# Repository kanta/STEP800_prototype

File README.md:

# STEP800_prototype

This repository has been retained for data storage, but is no longer being updated.

Please visit https://github.com/ponoor/STEP800.

---

8 axis stepper motor driver board which can control over Ethernet. The current firmware is based on [Open Sound Control](http://opensoundcontrol.org/) protocol.
[Arduino Zero](https://www.arduino.cc/en/Guide/ArduinoZero) and official [Ethernet library](https://www.arduino.cc/en/reference/ethernet) compatible.

Stepper driver chips are STMicroelectronics's [L6470](https://www.st.com/en/motor-drivers/l6470.html) which provide most of functionalities as a stepper driver.

# Repository Contents

# Documentation

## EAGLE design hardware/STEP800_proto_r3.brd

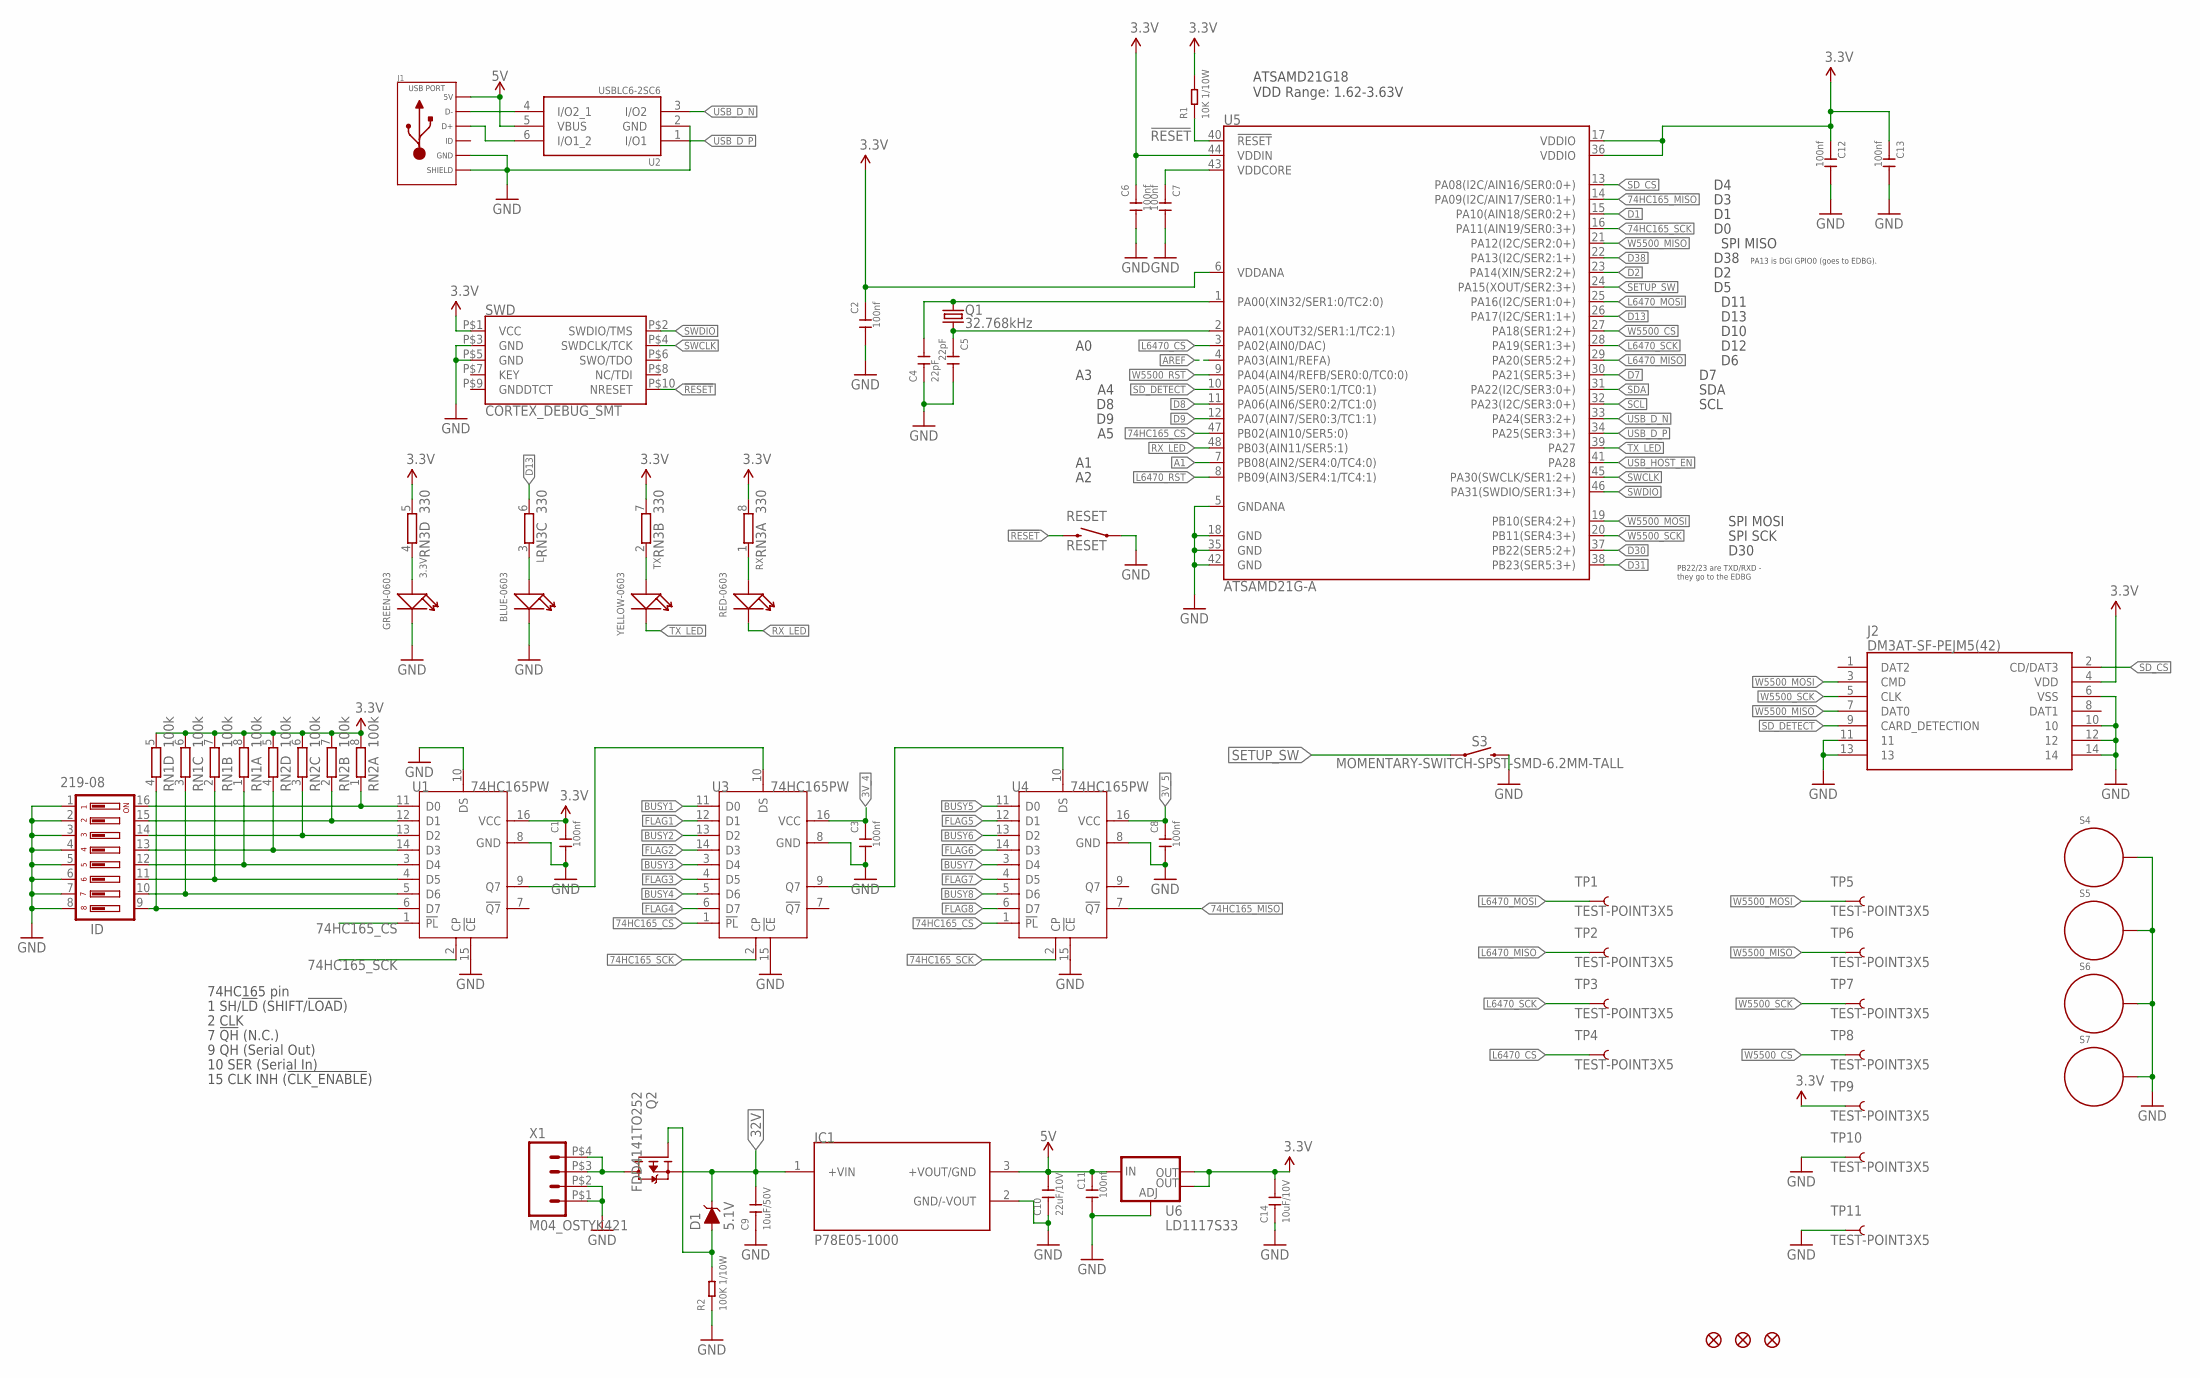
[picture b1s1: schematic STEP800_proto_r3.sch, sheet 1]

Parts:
3.3V: GREEN-0603; LED-0603
C1, C2, C3, C6, C7, C8, C11, C12, C13: 100nf; C0402
C4, C5: 22pF; C0402
C9: 10uF/50V; C1206
C10: 22uF/10V; C1206
C14: 10uF/10V; C0805
D1: 5.1V; SOD-323
FD1, FD2, FD3: FIDUCIAL1X2; FIDUCIAL-1X2
IC1: P78E05-1000; CONV_P78E05-1000
ID: 219-08; CTS-219-08
J1: USB_MICRO_10118193-0001LF; MICROUSB-FCI-PBAN
J2: DM3AT-SF-PEJM5(42); DM3ATSFPEJM542
L: BLUE-0603; LED-0603
Q1: 32.768kHz; FC-135
Q2: FDD4141TO252; TO252
R1: 10K 1/10W; R0603
R2: 100K 1/10W; R0603
RESET: RESET; TACTILE-SWITCH-SMD
RN1, RN2: 100k; CAY16_LONG_W
RN3: 330; CAY16_LONG_W
RX: RED-0603; LED-0603
S3: MOMENTARY-SWITCH-SPST-SMD-6.2MM-TALL; TACTILE_SWITCH_SMD_6.2MM_TALL
S4, S5, S6, S7: STANDOFF_ELECTRICAL; STANDOFF-ELECTRICAL
SWD: CORTEX_DEBUG_SMT; 20021121-00010C4LF
TP1, TP2, TP3, TP4, TP5, TP6, TP7, TP8, TP9, TP10, TP11: TEST-POINT3X5; PAD.03X.05
TX: YELLOW-0603; LED-0603
U1, U3, U4: 74HC165PW; TSSOP16
U2: USBLC6-2SC6; SOT23-6L
U5: ATSAMD21G-A; TQFP-48
U6: LD1117S33; SOT223
X1: M04_OSTYK421; OSTYK42104030

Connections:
3.3V: C1.1, C2.1, C6.1, C12.1, C13.1, C14.2, J2.4 (VDD), R1.2, RN1.5 (2), RN1.6 (2), RN1.7 (2), RN1.8 (2), RN2.5 (2), RN2.6 (2), RN2.7 (2), RN2.8 (2), RN3.5 (2), RN3.7 (2), RN3.8 (2), SWD.P$1 (VCC), TP9.P$1, U1.16 (VCC), U5.6 (VDDANA), U5.17 (VDDIO), U5.36 (VDDIO), U5.44 (VDDIN), U6.2 (OUT), U6.4 (OUT); also elsewhere on the board
3V_4: C3.1, U3.16 (VCC); also elsewhere on the board
3V_5: C8.1, U4.16 (VCC); also elsewhere on the board
5V: C10.2, C11.1, IC1.3 (+VOUT/GND), J1.1 (5V), U2.5 (VBUS), U6.3 (IN); also elsewhere on the board
32V: C9.2, D1.C, IC1.1 (+VIN), Q2.2 (S); also elsewhere on the board
74HC165_CS: U1.1 (!PL), U3.1 (!PL), U4.1 (!PL), U5.47 (PB02(AIN10/SER5:0))
74HC165_MISO: U4.7 (!Q7), U5.14 (PA09(I2C/AIN17/SER0:1+))
74HC165_SCK: U1.2 (CP), U3.2 (CP), U4.2 (CP), U5.16 (PA11(AIN19/SER0:3+))
!RESET: R1.1, RESET.3 (2), SWD.P$10 (NRESET), U5.40 (!RESET!)
A1: U5.7 (PB08(AIN2/SER4:0/TC4:0))
AREF: U5.4 (PA03(AIN1/REFA))
BUSY1: U3.11 (D0); also elsewhere on the board
BUSY2: U3.13 (D2); also elsewhere on the board
BUSY3: U3.3 (D4); also elsewhere on the board
BUSY4: U3.5 (D6); also elsewhere on the board
BUSY5: U4.11 (D0); also elsewhere on the board
BUSY6: U4.13 (D2); also elsewhere on the board
BUSY7: U4.3 (D4); also elsewhere on the board
BUSY8: U4.5 (D6); also elsewhere on the board
D1: U5.15 (PA10(AIN18/SER0:2+))
D2: U5.23 (PA14(XIN/SER2:2+))
D7: U5.30 (PA21(SER5:3+))
D8: U5.11 (PA06(AIN6/SER0:2/TC1:0))
D9: U5.12 (PA07(AIN7/SER0:3/TC1:1))
D13: RN3.6 (2), U5.26 (PA17(I2C/SER1:1+))
D30: U5.37 (PB22(SER5:2+))
D31: U5.38 (PB23(SER5:3+))
D38: U5.22 (PA13(I2C/SER2:1+))
D+1: J1.3 (D+), U2.6 (I/O1_2)
FLAG1: U3.12 (D1); also elsewhere on the board
FLAG2: U3.14 (D3); also elsewhere on the board
FLAG3: U3.4 (D5); also elsewhere on the board
FLAG4: U3.6 (D7); also elsewhere on the board
FLAG5: U4.12 (D1); also elsewhere on the board
FLAG6: U4.14 (D3); also elsewhere on the board
FLAG7: U4.4 (D5); also elsewhere on the board
FLAG8: U4.6 (D7); also elsewhere on the board
GND: 3.3V.-, C1.2, C2.2, C3.2, C4.1, C5.2, C6.2, C7.2, C8.2, C9.1, C10.1, C11.2, C12.2, C13.2, C14.1, IC1.2 (GND/-VOUT), ID.1, ID.2, ID.3, ID.4, ID.5, ID.6, ID.7, ID.8, J1.5 (GND), J1.S1 (SLD), J1.S2 (SLD), J1.S3 (SLD), J1.S4 (SLD), J1.S5 (SLD), J1.S6 (SLD), J1.S7 (SLD), J1.S8 (SLD), J2.6 (VSS), J2.10, J2.11, J2.12, J2.13, J2.14, L.-, R2.1, RESET.1, S3.B2 (2), S4.P1, S5.P1, S6.P1, S7.P1, SWD.P$3 (GND), SWD.P$5 (GND), TP10.P$1, TP11.P$1, U1.8 (GND), U1.10 (DS), U1.15 (!CE), U2.2 (GND), U3.8 (GND), U3.15 (!CE), U4.8 (GND), U4.15 (!CE), U5.5 (GNDANA), U5.18 (GND), U5.35 (GND), U5.42 (GND), U6.1 (ADJ), X1.P$1 (1), X1.P$2 (2); also elsewhere on the board
L6470_CS: TP4.P$1, U5.3 (PA02(AIN0/DAC)); also elsewhere on the board
L6470_MISO: TP2.P$1, U5.29 (PA20(SER5:2+)); also elsewhere on the board
L6470_MOSI: TP1.P$1, U5.25 (PA16(I2C/SER1:0+)); also elsewhere on the board
L6470_RST: U5.8 (PB09(AIN3/SER4:1/TC4:1)); also elsewhere on the board
L6470_SCK: TP3.P$1, U5.28 (PA19(SER1:3+)); also elsewhere on the board
unnamed: C4.2, Q1.P$2 (2), U5.1 (PA00(XIN32/SER1:0/TC2:0))
unnamed: ID.16, RN2.1, U1.11 (D0)
unnamed: D1.A, Q2.1 (G), R2.2
unnamed: ID.15, RN2.2 (1), U1.12 (D1)
unnamed: ID.14, RN2.3 (1), U1.13 (D2)
unnamed: C5.1, Q1.P$1 (1), U5.2 (PA01(XOUT32/SER1:1/TC2:1))
unnamed: U1.9 (Q7), U3.10 (DS)
unnamed: RN3.1, RX.+
unnamed: ID.13, RN2.4 (1), U1.14 (D3)
unnamed: ID.12, RN1.1, U1.3 (D4)
unnamed: ID.11, RN1.2 (1), U1.4 (D5)
unnamed: RN3.2 (1), TX.+
unnamed: L.+, RN3.3 (1)
unnamed: 3.3V.+, RN3.4 (1)
unnamed: J1.2 (D-), U2.4 (I/O2_1)
unnamed: ID.10, RN1.3 (1), U1.5 (D6)
unnamed: U3.9 (Q7), U4.10 (DS)
unnamed: ID.9, RN1.4 (1), U1.6 (D7)
RX_LED: RX.-, U5.48 (PB03(AIN11/SER5:1))
SCL: U5.32 (PA23(I2C/SER3:0+))
SDA: U5.31 (PA22(I2C/SER3:0+))
SD_CS: J2.2 (CD/DAT3), U5.13 (PA08(I2C/AIN16/SER0:0+))
SD_DETECT: J2.9 (CARD_DETECTION), U5.10 (PA05(AIN5/SER0:1/TC0:1))
SETUP_SW: S3.A2 (1), U5.24 (PA15(XOUT/SER2:3+))
SWCLK: SWD.P$4 (SWDCLK/TCK), U5.45 (PA30(SWCLK/SER1:2+))
SWDIO: SWD.P$2 (SWDIO/TMS), U5.46 (PA31(SWDIO/SER1:3+))
TX_LED: TX.-, U5.39 (PA27)
USB_D_N: U2.3 (I/O2), U5.33 (PA24(SER3:2+))
USB_D_P: U2.1 (I/O1), U5.34 (PA25(SER3:3+))
USB_HOST_EN: U5.41 (PA28)
VDDCORE1: C7.1, U5.43 (VDDCORE)
VRAW: Q2.3 (D), X1.P$3 (3), X1.P$4 (4)
W5500_CS: TP8.P$1, U5.27 (PA18(SER1:2+)); also elsewhere on the board
W5500_MISO: J2.7 (DAT0), TP6.P$1, U5.21 (PA12(I2C/SER2:0+)); also elsewhere on the board
W5500_MOSI: J2.3 (CMD), TP5.P$1, U5.19 (PB10(SER4:2+)); also elsewhere on the board
W5500_RST: U5.9 (PA04(AIN4/REFB/SER0:0/TC0:0)); also elsewhere on the board
W5500_SCK: J2.5 (CLK), TP7.P$1, U5.20 (PB11(SER4:3+)); also elsewhere on the board

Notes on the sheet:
PB22/23 are TXD/RXD - they go to the EDBG
PA13 is DGI GPIO0 (goes to EDBG).
ATSAMD21G18 VDD Range: 1.62-3.63V
D30
D12
D10
D11
D13
D38
SPI MISO
SPI MOSI
SPI SCK
SDA
SCL
1 SH/!LD! (SHIFT/!LOAD!)
2 CLK
7 !QH! (N.C.)
9 QH (Serial Out)
10 SER (Serial In)
15 CLK INH (!CLK_ENABLE!)
74HC165 pin

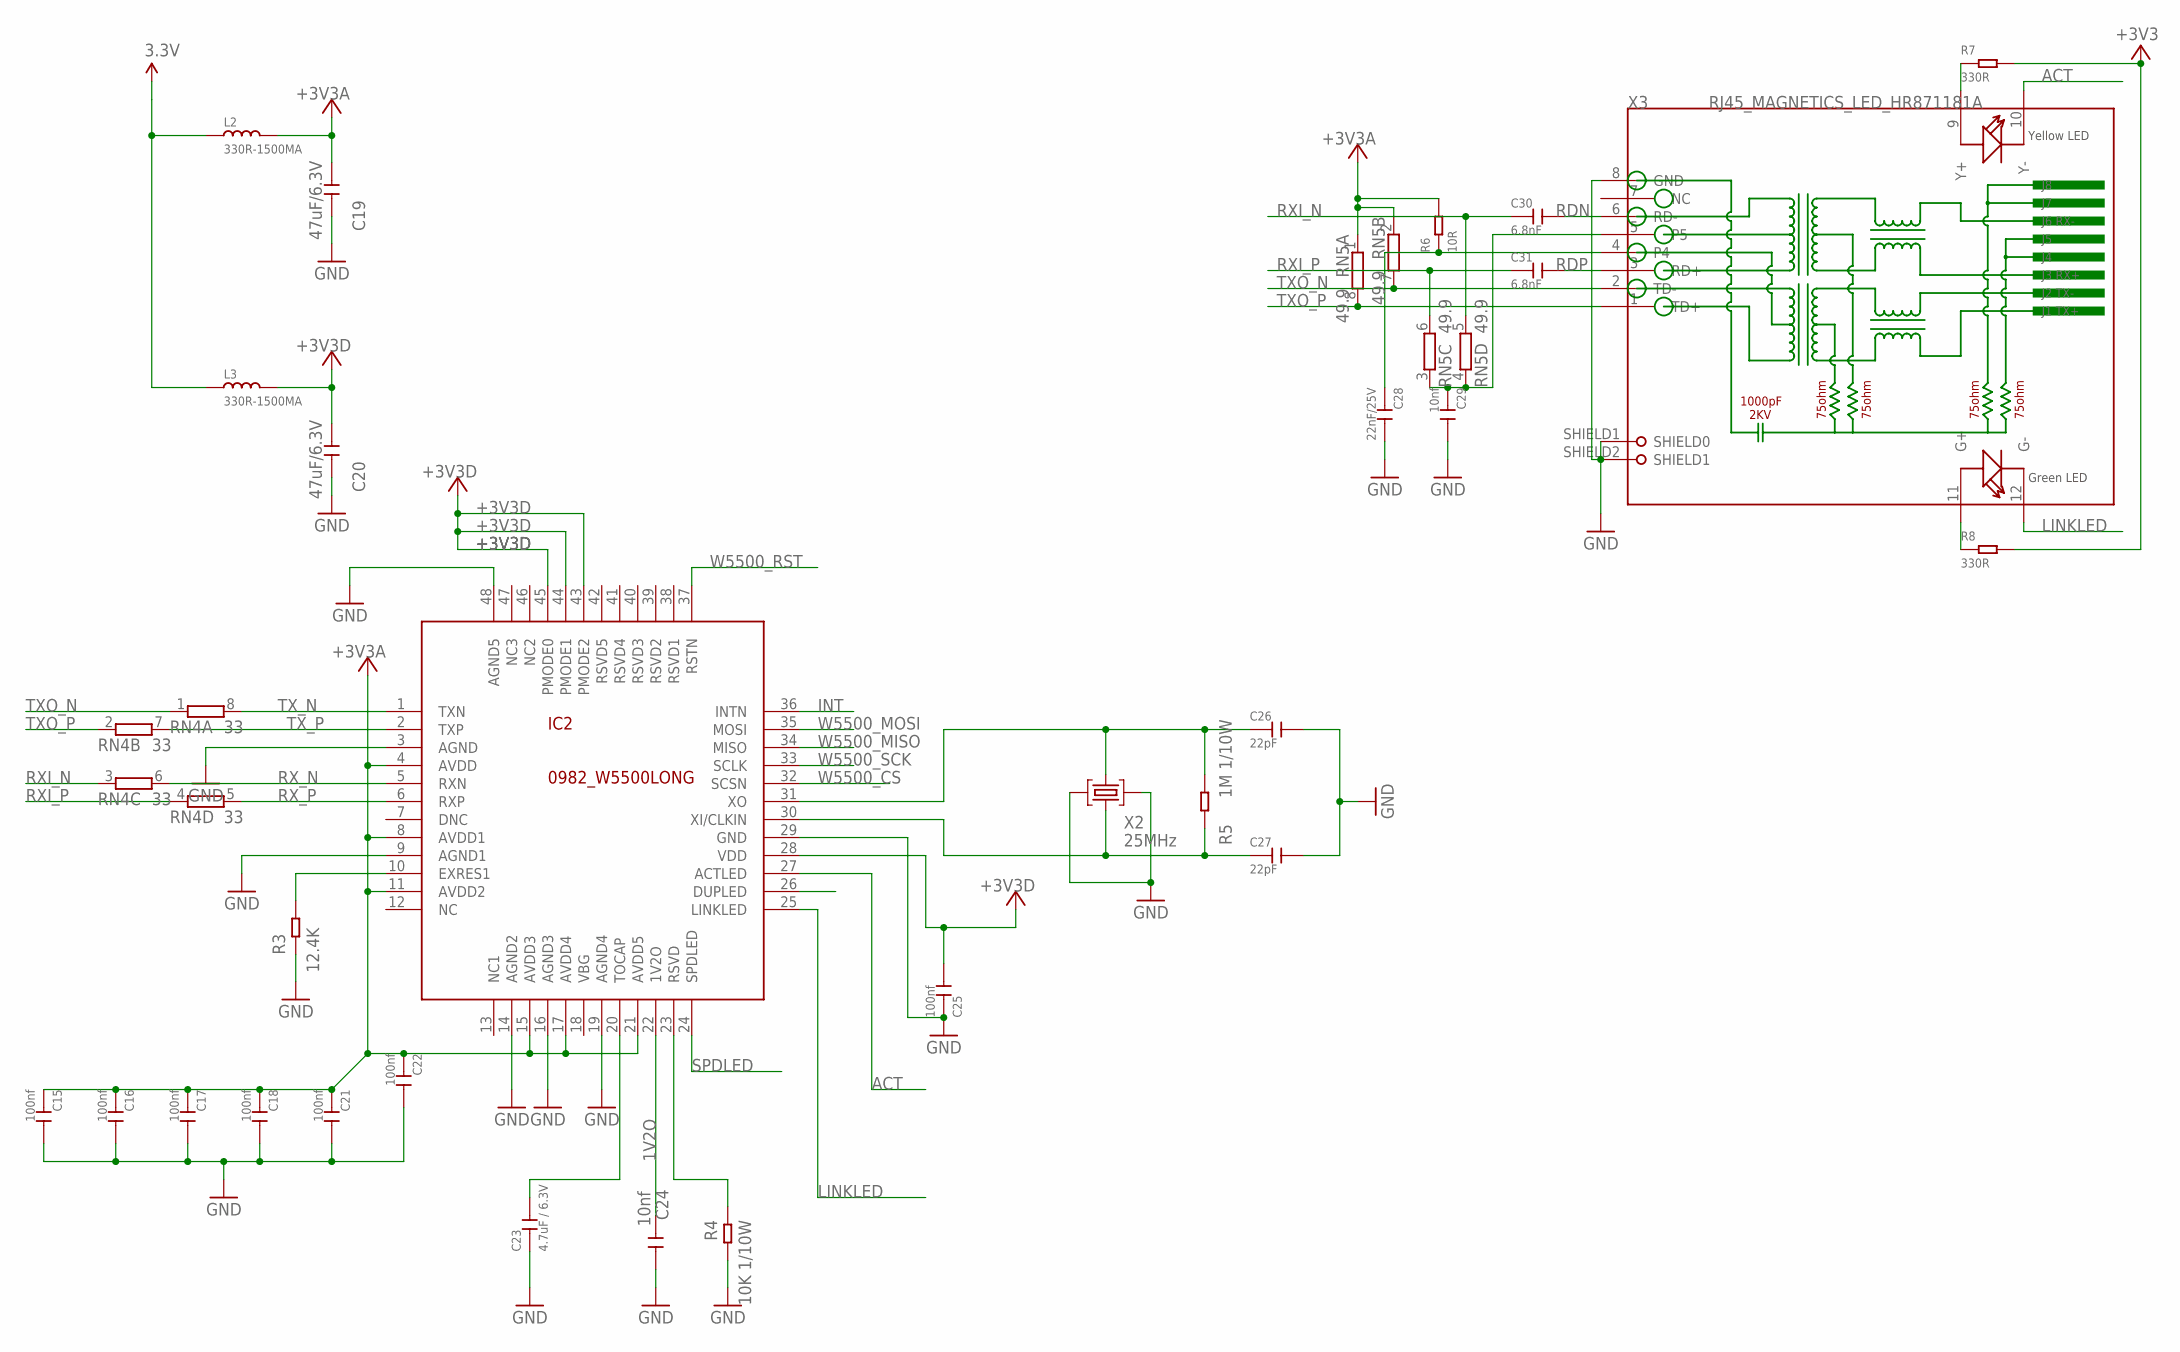
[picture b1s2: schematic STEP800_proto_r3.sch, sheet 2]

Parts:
C15, C16, C17, C18, C21, C22, C25: 100nf; C0402
C19, C20: 47uF/6.3V; C1206
C23: 4.7uF / 6.3V; C0603
C24, C29: 10nf; C0402
C26, C27: 22pF; C0402
C28: 22nF/25V; C0402
C30, C31: 6.8nF; C0402
IC2: 0982_W5500LONG; TQFP48-LONG
L2, L3: 330R-1500MA; L0805
R3: 12.4K; R0603
R4: 10K 1/10W; R0603
R5: 1M 1/10W; R0603
R6: 10R; R0603
R7, R8: 330R; R0603
RN4: 33; CAY16_LONG_W
RN5: 49.9; CAY16_LONG_W
X2: 25MHz; CRYSTAL-3.2-2.5
X3: RJ45_MAGNETICS_LED_HR871181A; HR871181A

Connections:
1V2O: C24.2, IC2.22 (1V2O)
3.3V: L2.1, L3.1, R7.2, R8.2; also elsewhere on the board
+3V3A: C15.1, C16.1, C17.1, C18.1, C19.1, C21.1, C22.1, IC2.4 (AVDD), IC2.8 (AVDD1), IC2.11 (AVDD2), IC2.15 (AVDD3), IC2.17 (AVDD4), IC2.21 (AVDD5), L2.2, R6.2, RN5.1, RN5.2 (1)
+3V3D: C20.1, C25.2, IC2.28 (VDD), IC2.43 (PMODE2), IC2.44 (PMODE1), IC2.45 (PMODE0), L3.2
ACT: IC2.27 (ACTLED), X3.10 (Y-)
FDXLED1: IC2.26 (DUPLED)
GND: C15.2, C16.2, C17.2, C18.2, C19.2, C20.2, C21.2, C22.2, C23.1, C24.1, C25.1, C26.2, C27.2, C28.2, C29.2, IC2.3 (AGND), IC2.9 (AGND1), IC2.14 (AGND2), IC2.16 (AGND3), IC2.19 (AGND4), IC2.29 (GND), IC2.48 (AGND5), R3.1, R4.1, X2.2 (GND), X2.4 (GND), X3.8 (GND), X3.SHIELD1 (SHIELD0), X3.SHIELD2 (SHIELD1); also elsewhere on the board
INT: IC2.36 (INTN)
LINKLED: IC2.25 (LINKLED), X3.12 (G-)
unnamed: C26.1, IC2.31 (XO), R5.1, X2.3 (C2)
unnamed: IC2.23 (RSVD), R4.2
unnamed: IC2.10 (EXRES1), R3.2
unnamed: C23.2, IC2.20 (TOCAP)
unnamed: C28.1, R6.1, X3.4
unnamed: C29.1, RN5.3 (1), RN5.4 (1), X3.5
unnamed: R7.1, X3.9 (Y+)
unnamed: R8.1, X3.11 (G+)
NC: IC2.12 (NC)
OSC2E1: C27.1, IC2.30 (XI/CLKIN), R5.2, X2.1 (C1)
RDN: C30.2, X3.6 (RD-)
RDP: C31.2, X3.3 (RD+)
RSVD1: IC2.38 (RSVD1)
RSVD2: IC2.39 (RSVD2)
RSVD3: IC2.40 (RSVD3)
RXI_N: C30.1, RN4.3 (1), RN5.5 (2)
RXI_P: C31.1, RN4.4 (1), RN5.6 (2)
RX_N: IC2.5 (RXN), RN4.6 (2)
RX_P: IC2.6 (RXP), RN4.5 (2)
SPDLED: IC2.24 (SPDLED)
TXO_N: RN4.1, RN5.7 (2), X3.2 (TD-)
TXO_P: RN4.2 (1), RN5.8 (2), X3.1 (TD+)
TX_N: IC2.1 (TXN), RN4.8 (2)
TX_P: IC2.2 (TXP), RN4.7 (2)
W5500_CS: IC2.32 (SCSN); also elsewhere on the board
W5500_MISO: IC2.34 (MISO); also elsewhere on the board
W5500_MOSI: IC2.35 (MOSI); also elsewhere on the board
W5500_RST: IC2.37 (RSTN); also elsewhere on the board
W5500_SCK: IC2.33 (SCLK); also elsewhere on the board

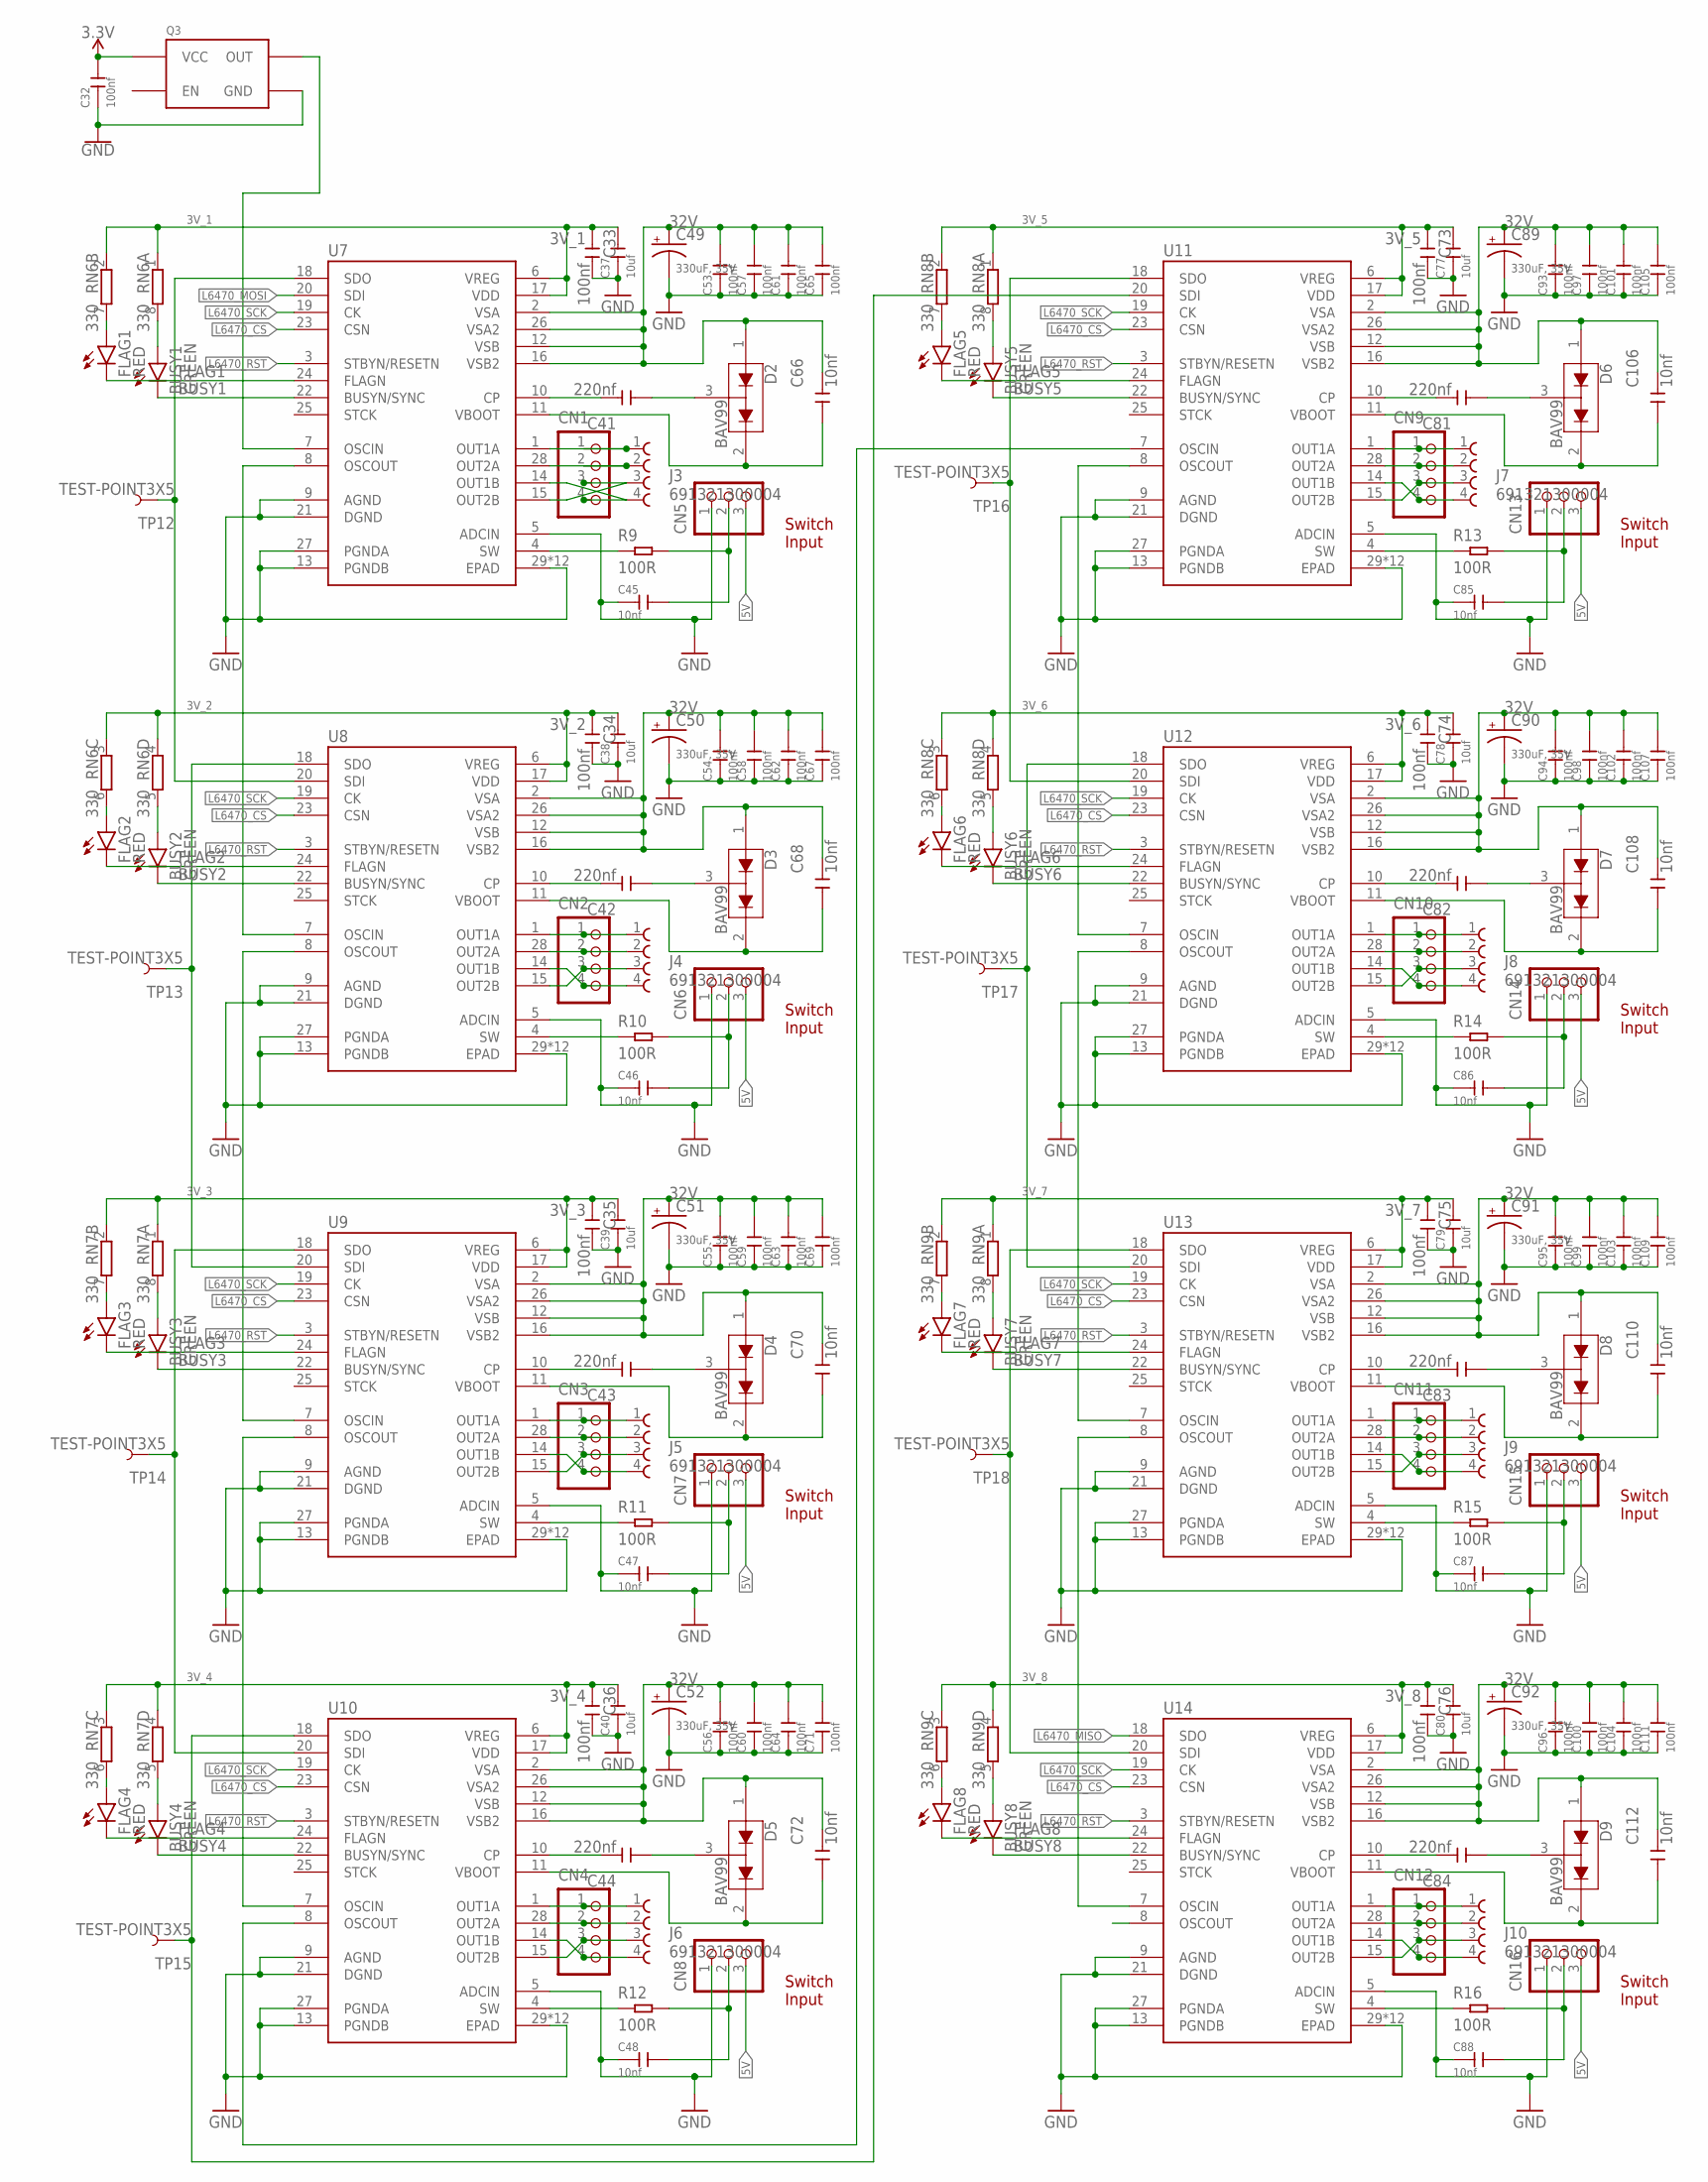
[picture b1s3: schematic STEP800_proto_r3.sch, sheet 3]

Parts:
BUSY1, BUSY2, BUSY3, BUSY4, BUSY5, BUSY6, BUSY7, BUSY8: GREEN; LED-0603
C32, C33, C34, C35, C36, C73, C74, C75, C76: 100nf; C0402
C37, C38, C39, C40, C77, C78, C79, C80: 10uf; C0805
C41, C42, C43, C44, C81, C82, C83, C84: 220nf; C0603
C45, C46, C47, C48, C66, C68, C70, C72, C85, C86, C87, C88, C106, C108, C110, C112: 10nf; C0402
C49, C50, C51, C52, C89, C90, C91, C92: 330uF, 35V; NICHICON_D10
C53, C54, C55, C56, C57, C58, C59, C60, C61, C62, C63, C64, C65, C67, C69, C71, C93, C94, C95, C96, C97, C98, C99, C100, C101, C102, C103, C104, C105, C107, C109, C111: 100nf; C0603
CN1, CN2, CN3, CN4, CN9, CN10, CN11, CN12: B4B-XASK-1
CN5, CN6, CN7, CN8, CN13, CN14, CN15, CN16: B3B-XASK-1
D2, D3, D4, D5, D6, D7, D8, D9: BAV99; SOT23-3
FLAG1, FLAG2, FLAG3, FLAG4, FLAG5, FLAG6, FLAG7, FLAG8: RED; LED-0603
J3, J4, J5, J6, J7, J8, J9, J10: 691321300004
Q3: CRYSTAL_OSC_SG5032; SG5032
R9, R10, R11, R12, R13, R14, R15, R16: 100R; R0603
RN6, RN7, RN8, RN9: 330; CAY16_LONG_W
TP12, TP13, TP14, TP15, TP16, TP17, TP18: TEST-POINT3X5; PAD.03X.05
U7, U8, U9, U10, U11, U12, U13, U14: L6470_THERMALVIA; HTSSOP28_VIA

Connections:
3.3V: C32.2, Q3.4 (VCC); also elsewhere on the board
3V_1: C33.1, C37.2, RN6.1, RN6.2 (1), U7.6 (VREG), U7.17 (VDD)
3V_2: C34.1, C38.2, RN6.3 (1), RN6.4 (1), U8.6 (VREG), U8.17 (VDD)
3V_3: C35.1, C39.2, RN7.1, RN7.2 (1), U9.6 (VREG), U9.17 (VDD)
3V_4: C36.1, C40.2, RN7.3 (1), RN7.4 (1), U10.6 (VREG), U10.17 (VDD); also elsewhere on the board
3V_5: C73.1, C77.2, RN8.1, RN8.2 (1), U11.6 (VREG), U11.17 (VDD); also elsewhere on the board
3V_6: C74.1, C78.2, RN8.3 (1), RN8.4 (1), U12.6 (VREG), U12.17 (VDD)
3V_7: C75.1, C79.2, RN9.1, RN9.2 (1), U13.6 (VREG), U13.17 (VDD)
3V_8: C76.1, C80.2, RN9.3 (1), RN9.4 (1), U14.6 (VREG), U14.17 (VDD)
5V: CN5.3, CN6.3, CN7.3, CN8.3, CN13.3, CN14.3, CN15.3, CN16.3; also elsewhere on the board
32V: C49.+, C50.+, C51.+, C52.+, C53.2, C54.2, C55.2, C56.2, C57.2, C58.2, C59.2, C60.2, C61.2, C62.2, C63.2, C64.2, C65.2, C66.2, C67.2, C68.2, C69.2, C70.2, C71.2, C72.2, C89.+, C90.+, C91.+, C92.+, C93.2, C94.2, C95.2, C96.2, C97.2, C98.2, C99.2, C100.2, C101.2, C102.2, C103.2, C104.2, C105.2, C106.2, C107.2, C108.2, C109.2, C110.2, C111.2, C112.2, D2.1 (A1), D3.1 (A1), D4.1 (A1), D5.1 (A1), D6.1 (A1), D7.1 (A1), D8.1 (A1), D9.1 (A1), U7.2 (VSA), U7.12 (VSB), U7.16 (VSB2), U7.26 (VSA2), U8.2 (VSA), U8.12 (VSB), U8.16 (VSB2), U8.26 (VSA2), U9.2 (VSA), U9.12 (VSB), U9.16 (VSB2), U9.26 (VSA2), U10.2 (VSA), U10.12 (VSB), U10.16 (VSB2), U10.26 (VSA2), U11.2 (VSA), U11.12 (VSB), U11.16 (VSB2), U11.26 (VSA2), U12.2 (VSA), U12.12 (VSB), U12.16 (VSB2), U12.26 (VSA2), U13.2 (VSA), U13.12 (VSB), U13.16 (VSB2), U13.26 (VSA2), U14.2 (VSA), U14.12 (VSB), U14.16 (VSB2), U14.26 (VSA2); also elsewhere on the board
BUSY1: BUSY1.C, U7.22 (BUSYN/SYNC); also elsewhere on the board
BUSY2: BUSY2.C, U8.22 (BUSYN/SYNC); also elsewhere on the board
BUSY3: BUSY3.C, U9.22 (BUSYN/SYNC); also elsewhere on the board
BUSY4: BUSY4.C, U10.22 (BUSYN/SYNC); also elsewhere on the board
BUSY5: BUSY5.C, U11.22 (BUSYN/SYNC); also elsewhere on the board
BUSY6: BUSY6.C, U12.22 (BUSYN/SYNC); also elsewhere on the board
BUSY7: BUSY7.C, U13.22 (BUSYN/SYNC); also elsewhere on the board
BUSY8: BUSY8.C, U14.22 (BUSYN/SYNC); also elsewhere on the board
FLAG1: FLAG1.C, U7.24 (FLAGN); also elsewhere on the board
FLAG2: FLAG2.C, U8.24 (FLAGN); also elsewhere on the board
FLAG3: FLAG3.C, U9.24 (FLAGN); also elsewhere on the board
FLAG4: FLAG4.C, U10.24 (FLAGN); also elsewhere on the board
FLAG5: FLAG5.C, U11.24 (FLAGN); also elsewhere on the board
FLAG6: FLAG6.C, U12.24 (FLAGN); also elsewhere on the board
FLAG7: FLAG7.C, U13.24 (FLAGN); also elsewhere on the board
FLAG8: FLAG8.C, U14.24 (FLAGN); also elsewhere on the board
GND: C32.1, C33.2, C34.2, C35.2, C36.2, C37.1, C38.1, C39.1, C40.1, C45.1, C46.1, C47.1, C48.1, C49.-, C50.-, C51.-, C52.-, C53.1, C54.1, C55.1, C56.1, C57.1, C58.1, C59.1, C60.1, C61.1, C62.1, C63.1, C64.1, C65.1, C67.1, C69.1, C71.1, C73.2, C74.2, C75.2, C76.2, C77.1, C78.1, C79.1, C80.1, C85.1, C86.1, C87.1, C88.1, C89.-, C90.-, C91.-, C92.-, C93.1, C94.1, C95.1, C96.1, C97.1, C98.1, C99.1, C100.1, C101.1, C102.1, C103.1, C104.1, C105.1, C107.1, C109.1, C111.1, CN5.1, CN6.1, CN7.1, CN8.1, CN13.1, CN14.1, CN15.1, CN16.1, Q3.2 (GND), U7.5 (ADCIN), U7.9 (AGND), U7.13 (PGNDB), U7.21 (DGND), U7.27 (PGNDA), U7.29 (EPAD), U7.VIA1 (EPAD), U7.VIA2 (EPAD), U7.VIA3 (EPAD), U7.VIA4 (EPAD), U7.VIA5 (EPAD), U7.VIA6 (EPAD), U7.VIA7 (EPAD), U7.VIA8 (EPAD), U7.VIA9 (EPAD), U7.VIA10 (EPAD), U7.VIA11 (EPAD), U8.5 (ADCIN), U8.9 (AGND), U8.13 (PGNDB), U8.21 (DGND), U8.27 (PGNDA), U8.29 (EPAD), U8.VIA1 (EPAD), U8.VIA2 (EPAD), U8.VIA3 (EPAD), U8.VIA4 (EPAD), U8.VIA5 (EPAD), U8.VIA6 (EPAD), U8.VIA7 (EPAD), U8.VIA8 (EPAD), U8.VIA9 (EPAD), U8.VIA10 (EPAD), U8.VIA11 (EPAD), U9.5 (ADCIN), U9.9 (AGND), U9.13 (PGNDB), U9.21 (DGND), U9.27 (PGNDA), U9.29 (EPAD), U9.VIA1 (EPAD), U9.VIA2 (EPAD), U9.VIA3 (EPAD), U9.VIA4 (EPAD), U9.VIA5 (EPAD), U9.VIA6 (EPAD), U9.VIA7 (EPAD), U9.VIA8 (EPAD), U9.VIA9 (EPAD), U9.VIA10 (EPAD), U9.VIA11 (EPAD), U10.5 (ADCIN), U10.9 (AGND), U10.13 (PGNDB), U10.21 (DGND), U10.27 (PGNDA), U10.29 (EPAD), U10.VIA1 (EPAD), U10.VIA2 (EPAD), U10.VIA3 (EPAD), U10.VIA4 (EPAD), U10.VIA5 (EPAD), U10.VIA6 (EPAD), U10.VIA7 (EPAD), U10.VIA8 (EPAD), U10.VIA9 (EPAD), U10.VIA10 (EPAD), U10.VIA11 (EPAD), U11.5 (ADCIN), U11.9 (AGND), U11.13 (PGNDB), U11.21 (DGND), U11.27 (PGNDA), U11.29 (EPAD), U11.VIA1 (EPAD), U11.VIA2 (EPAD), U11.VIA3 (EPAD), U11.VIA4 (EPAD), U11.VIA5 (EPAD), U11.VIA6 (EPAD), U11.VIA7 (EPAD), U11.VIA8 (EPAD), U11.VIA9 (EPAD), U11.VIA10 (EPAD), U11.VIA11 (EPAD), U12.5 (ADCIN), U12.9 (AGND), U12.13 (PGNDB), U12.21 (DGND), U12.27 (PGNDA), U12.29 (EPAD), U12.VIA1 (EPAD), U12.VIA2 (EPAD), U12.VIA3 (EPAD), U12.VIA4 (EPAD), U12.VIA5 (EPAD), U12.VIA6 (EPAD), U12.VIA7 (EPAD), U12.VIA8 (EPAD), U12.VIA9 (EPAD), U12.VIA10 (EPAD), U12.VIA11 (EPAD), U13.5 (ADCIN), U13.9 (AGND), U13.13 (PGNDB), U13.21 (DGND), U13.27 (PGNDA), U13.29 (EPAD), U13.VIA1 (EPAD), U13.VIA2 (EPAD), U13.VIA3 (EPAD), U13.VIA4 (EPAD), U13.VIA5 (EPAD), U13.VIA6 (EPAD), U13.VIA7 (EPAD), U13.VIA8 (EPAD), U13.VIA9 (EPAD), U13.VIA10 (EPAD), U13.VIA11 (EPAD), U14.5 (ADCIN), U14.9 (AGND), U14.13 (PGNDB), U14.21 (DGND), U14.27 (PGNDA), U14.29 (EPAD), U14.VIA1 (EPAD), U14.VIA2 (EPAD), U14.VIA3 (EPAD), U14.VIA4 (EPAD), U14.VIA5 (EPAD), U14.VIA6 (EPAD), U14.VIA7 (EPAD), U14.VIA8 (EPAD), U14.VIA9 (EPAD), U14.VIA10 (EPAD), U14.VIA11 (EPAD); also elsewhere on the board
L6470_CS: U7.23 (CSN), U8.23 (CSN), U9.23 (CSN), U10.23 (CSN), U11.23 (CSN), U12.23 (CSN), U13.23 (CSN), U14.23 (CSN); also elsewhere on the board
L6470_MISO: U14.18 (SDO); also elsewhere on the board
L6470_MOSI: U7.20 (SDI); also elsewhere on the board
L6470_RST: U7.3 (STBYN/RESETN), U8.3 (STBYN/RESETN), U9.3 (STBYN/RESETN), U10.3 (STBYN/RESETN), U11.3 (STBYN/RESETN), U12.3 (STBYN/RESETN), U13.3 (STBYN/RESETN), U14.3 (STBYN/RESETN); also elsewhere on the board
L6470_SCK: U7.19 (CK), U8.19 (CK), U9.19 (CK), U10.19 (CK), U11.19 (CK), U12.19 (CK), U13.19 (CK), U14.19 (CK); also elsewhere on the board
unnamed: C41.2, U7.10 (CP)
unnamed: C41.1, D2.3 (COM)
unnamed: C66.1, D2.2 (C2), U7.11 (VBOOT)
unnamed: R9.1, U7.4 (SW)
unnamed: BUSY1.A, RN6.8 (2)
unnamed: FLAG1.A, RN6.7 (2)
unnamed: C45.2, CN5.2, R9.2
unnamed: CN1.1, J3.1, U7.1 (OUT1A)
unnamed: CN1.2, J3.2, U7.28 (OUT2A)
unnamed: CN1.4, J3.4, U7.14 (OUT1B)
unnamed: CN1.3, J3.3, U7.15 (OUT2B)
unnamed: TP12.P$1, U7.18 (SDO), U8.20 (SDI)
unnamed: C42.2, U8.10 (CP)
unnamed: C42.1, D3.3 (COM)
unnamed: C68.1, D3.2 (C2), U8.11 (VBOOT)
unnamed: R10.1, U8.4 (SW)
unnamed: BUSY2.A, RN6.5 (2)
unnamed: FLAG2.A, RN6.6 (2)
unnamed: C46.2, CN6.2, R10.2
unnamed: CN2.1, J4.1, U8.1 (OUT1A)
unnamed: CN2.2, J4.2, U8.28 (OUT2A)
unnamed: CN2.4, J4.4, U8.14 (OUT1B)
unnamed: CN2.3, J4.3, U8.15 (OUT2B)
unnamed: TP13.P$1, U8.18 (SDO), U9.20 (SDI)
unnamed: C43.2, U9.10 (CP)
unnamed: C43.1, D4.3 (COM)
unnamed: C70.1, D4.2 (C2), U9.11 (VBOOT)
unnamed: R11.1, U9.4 (SW)
unnamed: BUSY3.A, RN7.8 (2)
unnamed: FLAG3.A, RN7.7 (2)
unnamed: C47.2, CN7.2, R11.2
unnamed: CN3.1, J5.1, U9.1 (OUT1A)
unnamed: CN3.2, J5.2, U9.28 (OUT2A)
unnamed: CN3.4, J5.4, U9.14 (OUT1B)
unnamed: CN3.3, J5.3, U9.15 (OUT2B)
unnamed: TP14.P$1, U9.18 (SDO), U10.20 (SDI)
unnamed: C44.2, U10.10 (CP)
unnamed: C44.1, D5.3 (COM)
unnamed: C72.1, D5.2 (C2), U10.11 (VBOOT)
unnamed: R12.1, U10.4 (SW)
unnamed: BUSY4.A, RN7.5 (2)
unnamed: FLAG4.A, RN7.6 (2)
unnamed: C48.2, CN8.2, R12.2
unnamed: CN4.1, J6.1, U10.1 (OUT1A)
unnamed: CN4.2, J6.2, U10.28 (OUT2A)
unnamed: CN4.4, J6.4, U10.14 (OUT1B)
unnamed: CN4.3, J6.3, U10.15 (OUT2B)
unnamed: TP15.P$1, U10.18 (SDO), U11.20 (SDI)
unnamed: C81.2, U11.10 (CP)
unnamed: C81.1, D6.3 (COM)
unnamed: C106.1, D6.2 (C2), U11.11 (VBOOT)
unnamed: R13.1, U11.4 (SW)
unnamed: BUSY5.A, RN8.8 (2)
unnamed: FLAG5.A, RN8.7 (2)
unnamed: C85.2, CN13.2, R13.2
unnamed: CN9.1, J7.1, U11.1 (OUT1A)
unnamed: CN9.2, J7.2, U11.28 (OUT2A)
unnamed: CN9.4, J7.4, U11.14 (OUT1B)
unnamed: CN9.3, J7.3, U11.15 (OUT2B)
unnamed: TP16.P$1, U11.18 (SDO), U12.20 (SDI)
unnamed: C82.2, U12.10 (CP)
unnamed: C82.1, D7.3 (COM)
unnamed: C108.1, D7.2 (C2), U12.11 (VBOOT)
unnamed: R14.1, U12.4 (SW)
unnamed: BUSY6.A, RN8.5 (2)
unnamed: FLAG6.A, RN8.6 (2)
unnamed: C86.2, CN14.2, R14.2
unnamed: CN10.1, J8.1, U12.1 (OUT1A)
unnamed: CN10.2, J8.2, U12.28 (OUT2A)
unnamed: CN10.4, J8.4, U12.14 (OUT1B)
unnamed: CN10.3, J8.3, U12.15 (OUT2B)
unnamed: TP17.P$1, U12.18 (SDO), U13.20 (SDI)
unnamed: C83.2, U13.10 (CP)
unnamed: C83.1, D8.3 (COM)
unnamed: C110.1, D8.2 (C2), U13.11 (VBOOT)
unnamed: R15.1, U13.4 (SW)
unnamed: BUSY7.A, RN9.8 (2)
unnamed: FLAG7.A, RN9.7 (2)
unnamed: C87.2, CN15.2, R15.2
unnamed: CN11.1, J9.1, U13.1 (OUT1A)
unnamed: CN11.2, J9.2, U13.28 (OUT2A)
unnamed: CN11.4, J9.4, U13.14 (OUT1B)
unnamed: CN11.3, J9.3, U13.15 (OUT2B)
unnamed: TP18.P$1, U13.18 (SDO), U14.20 (SDI)
unnamed: C84.2, U14.10 (CP)
unnamed: C84.1, D9.3 (COM)
unnamed: C112.1, D9.2 (C2), U14.11 (VBOOT)
unnamed: R16.1, U14.4 (SW)
unnamed: BUSY8.A, RN9.5 (2)
unnamed: FLAG8.A, RN9.6 (2)
unnamed: C88.2, CN16.2, R16.2
unnamed: CN12.1, J10.1, U14.1 (OUT1A)
unnamed: CN12.2, J10.2, U14.28 (OUT2A)
unnamed: CN12.4, J10.4, U14.14 (OUT1B)
unnamed: CN12.3, J10.3, U14.15 (OUT2B)
OSCOUT2: U7.8 (OSCOUT), U8.7 (OSCIN)
OSCOUT4: U8.8 (OSCOUT), U9.7 (OSCIN)
OSCOUT6: U9.8 (OSCOUT), U10.7 (OSCIN)
OSCOUT8: U10.8 (OSCOUT), U11.7 (OSCIN)
OSCOUT10: U11.8 (OSCOUT), U12.7 (OSCIN)
OSCOUT12: U12.8 (OSCOUT), U13.7 (OSCIN)
OSCOUT14: U13.8 (OSCOUT), U14.7 (OSCIN)
OSCOUT16: U14.8 (OSCOUT)
QGOUT1: Q3.3 (OUT), U7.7 (OSCIN)

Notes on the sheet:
Switch Input

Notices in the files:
parts and their libraries:
SparkFun-Electromechanical: Licensing: Creative Commons ShareAlike 4.0 International - https://creativecommons.org/licenses/by-sa/4.0
